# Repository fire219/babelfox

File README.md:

**NOTE: This project is not quite ready for prime time. Everything could be subject to change; build at your own risk. More documentation will come on full release.**

## What is this?
**BabelFox** is a project to create an energy efficient yet high performance Meshtastic "remote gateway node" -- one which not only has a wide TX/RX range on the mesh, but also can bridge the gap to other communication protocols, *without the need for any additional equipment*. It is equipped with a LoRA module based on the **Semtech LR1121** chip, which not only provides better RX performance than the standard SX1262 used by most Meshtastic hardware, but also includes 2.4GHz LoRA capability. It is also equipped with a **SIMCom SIM7022** LTE modem, which provides low power NB-IoT internet connectivity, with global cellular band support.

## Specifications
**Form factor:** RPi compatible (85x56mm, with 58x49mm spaced mounting holes)

**Main Processor:** Luckfox Pico (based on Rockchip RV1103)

**LoRA Radio:** EByte E80-900 (based on Semtech LR1121)

**900MHz Amplifier:** EByte E21-900 1W PA/LNA

**Cell Radio:** SIMCom SIM7022

**Max LoRA TX Power:** 30dBm @ 900MHz, 13dBm @ 2.4GHz

**Power Source:** USB-C (5V only), 3.7V LiPo, 8-18V VDC

**Power Consumption:** ~5W peak, <3W nominal

## License

**BabelFox** is licensed under the CERN OHL v2 Strongly Reciprocal license. See the *LICENSE* file for more information.

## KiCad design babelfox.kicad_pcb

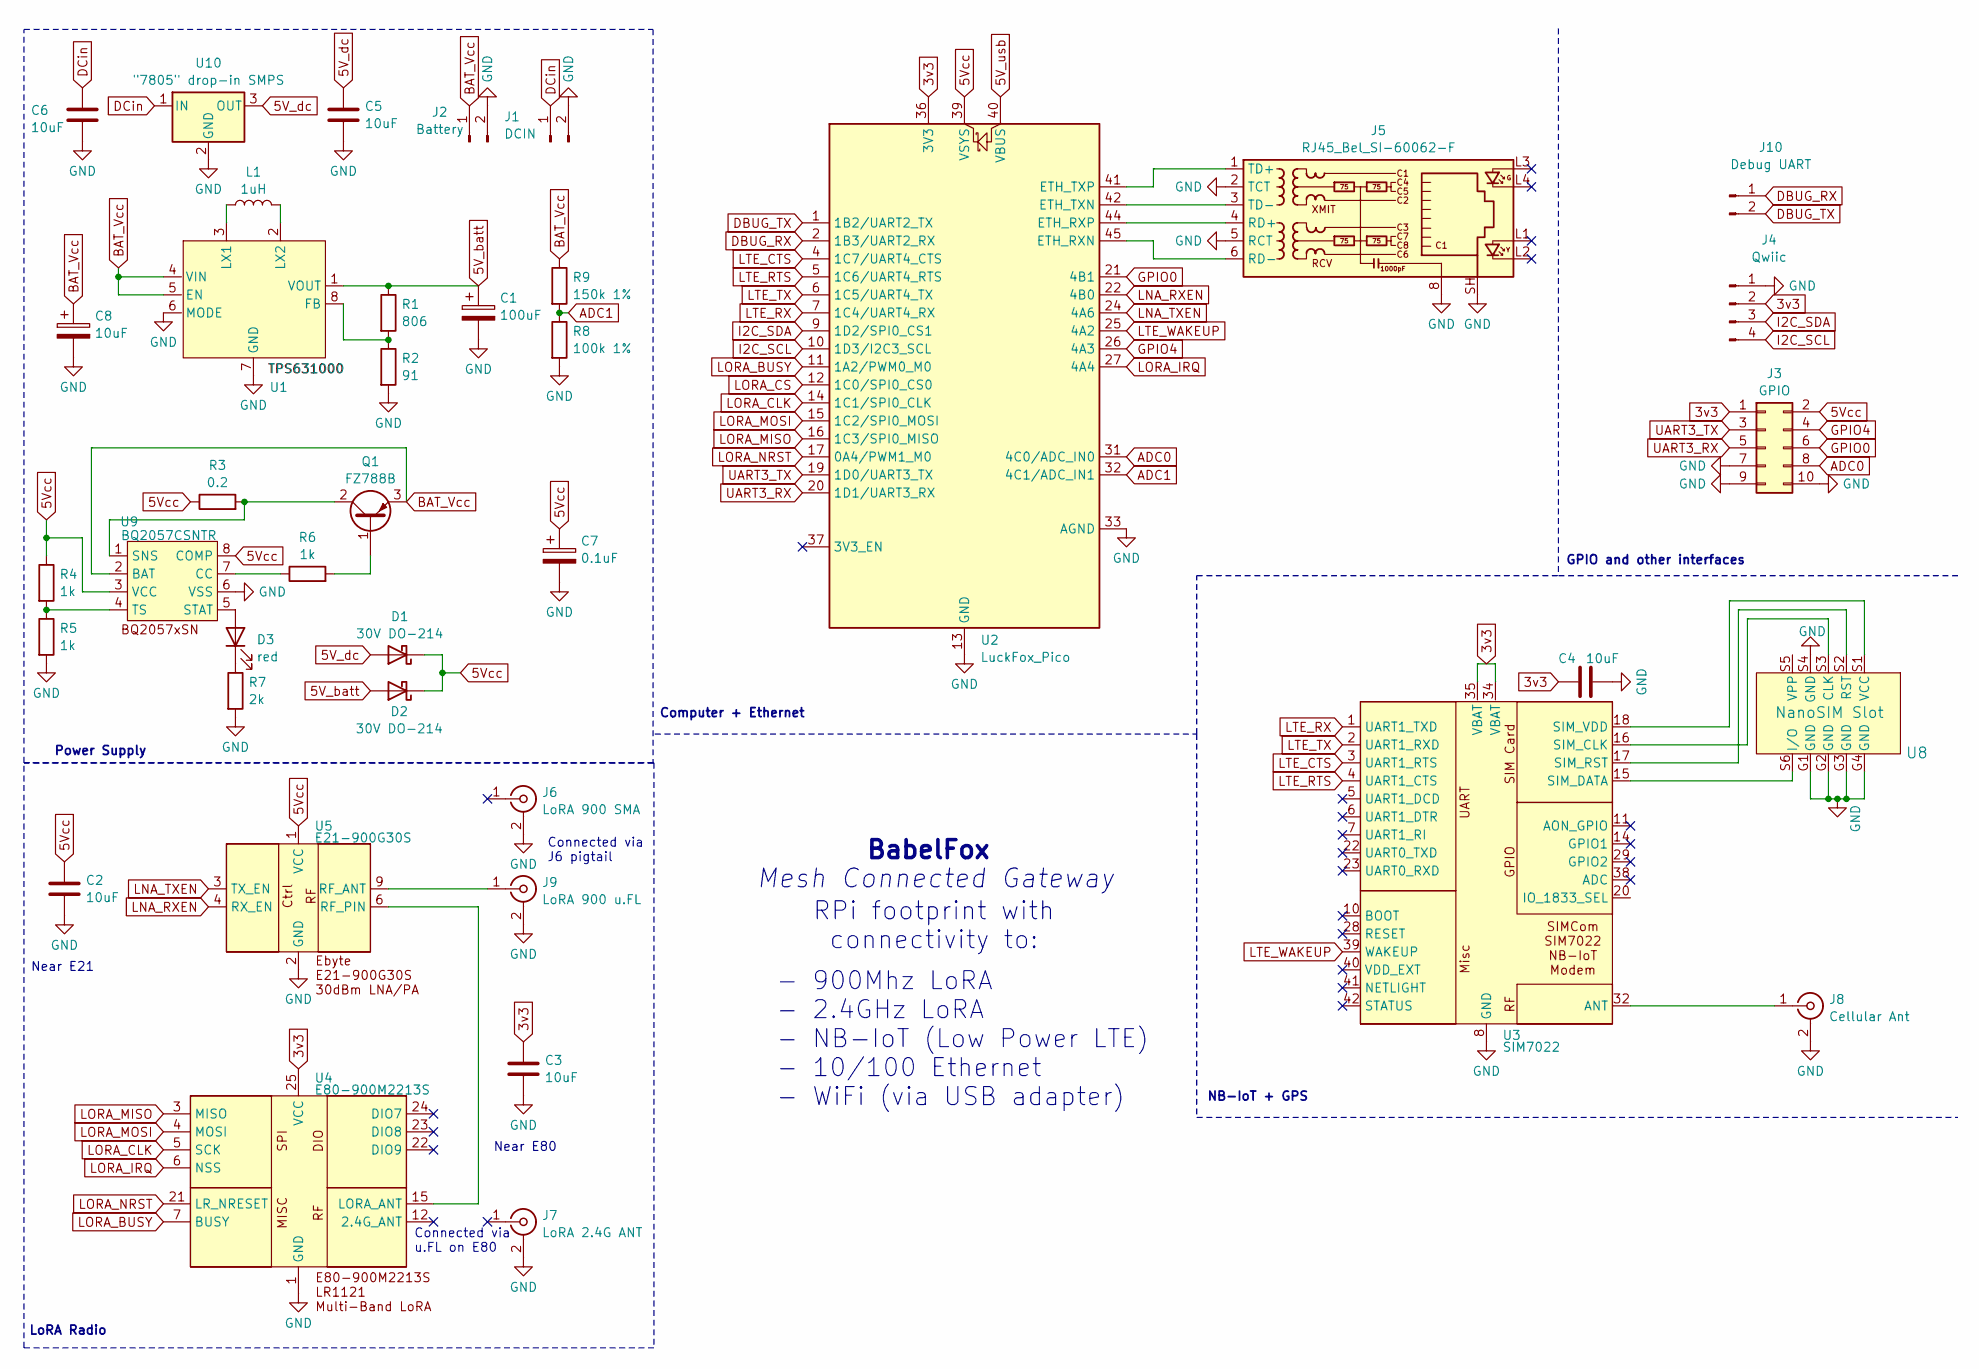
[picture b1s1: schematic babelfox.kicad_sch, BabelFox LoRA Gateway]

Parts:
C1: 100uF; C_0805_2012Metric_Pad1.18x1.45mm_HandSolder; LCSC C141660
C2, C3, C4, C5, C6, C8: 10uF; C_0805_2012Metric_Pad1.18x1.45mm_HandSolder; LCSC C15850
C7: 0.1uF; C_0805_2012Metric_Pad1.18x1.45mm_HandSolder; LCSC C17604
D1, D2: 30V DO-214; D_SMA_Handsoldering; LCSC C511853
D3: red; LED_0805_2012Metric_Pad1.15x1.40mm_HandSolder; LCSC C5156920
J1: DCIN; JST_EH_B2B-EH-A_1x02_P2.50mm_Vertical
J2: Battery; Molex_PicoBlade_53047-0210_1x02_P1.25mm_Vertical
J3: GPIO; PinHeader_2x05_P2.54mm_Vertical
J4: Qwiic; JST_SH_BM04B-SRSS-TB_1x04-1MP_P1.00mm_Vertical
J5: RJ45_Bel_SI-60062-F
J6: LoRA 900 SMA; SMA-TH_2LC15SF025
J7: LoRA 2.4G ANT; SMA-TH_2LC15SF025
J8: Cellular Ant; SMA_Amphenol_132203-12_Horizontal
J9: LoRA 900 u.FL; U.FL_Hirose_U.FL-R-SMT-1_Vertical; LCSC C88373
J10: Debug UART; PinSocket_1x02_P2.54mm_Vertical
L1: 1uH; L_1008_2520Metric_Pad1.43x2.20mm_HandSolder; LCSC C76827
Q1: FZ788B; SOT-223; LCSC C141330
R1: 806; R_0805_2012Metric_Pad1.20x1.40mm_HandSolder; LCSC C2999620
R2: 91; R_0805_2012Metric_Pad1.20x1.40mm_HandSolder; LCSC C4407
R3: 0.2; R_0805_2012Metric_Pad1.20x1.40mm_HandSolder; LCSC C44051
R4, R5, R6: 1k; R_0805_2012Metric_Pad1.20x1.40mm_HandSolder; LCSC C17513
R7: 2k; R_0805_2012Metric_Pad1.20x1.40mm_HandSolder
R8: 100k 1%; R_0805_2012Metric_Pad1.20x1.40mm_HandSolder; LCSC C25611
R9: 150k 1%; R_0805_2012Metric_Pad1.20x1.40mm_HandSolder; LCSC C17470
U1: TPS631000; SOT-583-8; LCSC C5219190
U2: LuckFox_Pico
U3: SIM7022; SIMCom_SIM7022
U4: E80-900M2213S; E80-x00M2213S
U5: E21-900G30S; E21-x00G30S
U8: NanoSIM Slot; 1042240820_MOL; LCSC C585349
U9: BQ2057CSNTR; SOIC-8_3.9x4.9mm_P1.27mm; LCSC C2866550
U10: "7805" drop-in SMPS; Converter_DCDC_RECOM_R-78E-0.5_THT

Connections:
3v3: C3.1, C4.1, J3.1, J4.2, U2.36 (3V3), U3.34 (VBAT), U3.35 (VBAT), U4.25 (VCC)
5V_batt: C1.1, D2.2 (A), R1.1, U1.1 (VOUT)
5V_dc: C5.1, D1.2 (A), U10.3 (OUT)
5V_usb: U2.40 (VBUS)
5Vcc: C2.1, C7.1, D1.1 (K), D2.1 (K), J3.2, R3.1, R4.1, U2.39 (VSYS), U5.1 (VCC), U9.3 (VCC), U9.8 (COMP)
ADC0: J3.8, U2.31 (4C0/ADC_IN0)
ADC1: R8.1, R9.2, U2.32 (4C1/ADC_IN1)
BAT_Vcc: C8.1, J2.1, Q1.3 (E), R9.1, U1.4 (VIN), U1.5 (EN), U9.2 (BAT)
DBUG_RX: J10.1, U2.2 (1B3/UART2_RX)
DBUG_TX: J10.2, U2.1 (1B2/UART2_TX)
DCin: C6.1, J1.1, U10.1 (IN)
GND: C1.2, C2.2, C3.2, C4.2, C5.2, C6.2, C7.2, C8.2, J1.2, J2.2, J3.7, J3.9, J3.10, J4.1, J5.2 (TCT), J5.5 (RCT), J5.8, J5.SH, J6.2 (Ext), J7.2 (Ext), J8.2 (Ext), J9.2 (Ext), R2.2, R5.2, R7.2, R8.2, U1.6 (MODE), U1.7 (GND), U2.3 (GND), U2.8 (GND), U2.13 (GND), U2.18 (GND), U2.23 (GND), U2.28 (GND), U2.33 (AGND), U2.38 (GND), U2.43 (GND), U3.8 (GND), U3.13 (GND), U3.19 (GND), U3.21 (GND), U3.27 (GND), U3.30 (GND), U3.31 (GND), U3.33 (GND), U3.36 (GND), U3.37 (GND), U4.1 (GND), U4.8 (GND), U4.11 (GND), U4.13 (GND), U4.14 (GND), U4.16 (GND), U4.19 (GND), U4.26 (GND), U5.2 (GND), U5.5 (GND), U5.7 (GND), U5.8 (GND), U5.10 (GND), U8.G1 (GND), U8.G2 (GND), U8.G3 (GND), U8.G4 (GND), U8.S4 (GND), U9.6 (VSS), U10.2 (GND)
GPIO0: J3.6, U2.21 (4B1)
GPIO4: J3.4, U2.26 (4A3)
I2C_SCL: J4.4, U2.10 (1D3/I2C3_SCL)
I2C_SDA: J4.3, U2.9 (1D2/SPI0_CS1)
LNA_RXEN: U2.22 (4B0), U5.4 (RX_EN)
LNA_TXEN: U2.24 (4A6), U5.3 (TX_EN)
LORA_BUSY: U2.11 (1A2/PWM0_M0), U4.7 (BUSY)
LORA_CLK: U2.14 (1C1/SPI0_CLK), U4.5 (SCK)
LORA_CS: U2.12 (1C0/SPI0_CS0)
LORA_IRQ: U2.27 (4A4), U4.6 (NSS)
LORA_MISO: U2.16 (1C3/SPI0_MISO), U4.3 (MISO)
LORA_MOSI: U2.15 (1C2/SPI0_MOSI), U4.4 (MOSI)
LORA_NRST: U2.17 (0A4/PWM1_M0), U4.21 (LR_NRESET)
LTE_CTS: U2.4 (1C7/UART4_CTS), U3.3 (UART1_RTS)
LTE_RTS: U2.5 (1C6/UART4_RTS), U3.4 (UART1_CTS)
LTE_RX: U2.7 (1C4/UART4_RX), U3.1 (UART1_TXD)
LTE_TX: U2.6 (1C5/UART4_TX), U3.2 (UART1_RXD)
LTE_WAKEUP: U2.25 (4A2), U3.39 (WAKEUP)
unnamed: D3.2 (A), U9.5 (STAT)
unnamed: D3.1 (K), R7.1
unnamed: J5.4 (RD+), U2.44 (ETH_RXP)
unnamed: J5.6 (RD-), U2.45 (ETH_RXN)
unnamed: J5.1 (TD+), U2.41 (ETH_TXP)
unnamed: J5.3 (TD-), U2.42 (ETH_TXN)
unnamed: J8.1 (In), U3.32 (ANT)
unnamed: J9.1 (In), U5.9 (RF_ANT)
unnamed: Q1.1 (B), R6.2
unnamed: Q1.2 (C), R3.2, U9.1 (SNS)
unnamed: R1.2, R2.1, U1.8 (FB)
unnamed: L1.1, U1.3 (LX1)
unnamed: L1.2, U1.2 (LX2)
unnamed: U3.16 (SIM_CLK), U8.S3 (CLK)
unnamed: U3.15 (SIM_DATA), U8.S6 (I/O)
unnamed: U3.17 (SIM_RST), U8.S2 (RST)
unnamed: U3.18 (SIM_VDD), U8.S1 (VCC)
unnamed: U4.15 (LORA_ANT), U5.6 (RF_PIN)
unnamed: R6.1, U9.7 (CC)
unnamed: R4.2, R5.1, U9.4 (TS)
UART3_RX: J3.5, U2.20 (1D1/UART3_RX)
UART3_TX: J3.3, U2.19 (1D0/UART3_TX)

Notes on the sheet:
Connected via J6 pigtail
Near E21
RPi footprint with connectivity to:
NB-IoT + GPS
Mesh Connected Gateway
Computer + Ethernet
Power Supply
Near E80
LoRA Radio
Connected via u.FL on E80
BabelFox
- 900Mhz LoRA - 2.4GHz LoRA - NB-IoT (Low Power LTE) - 10/100 Ethernet - WiFi (via USB adapter)
GPIO and other interfaces

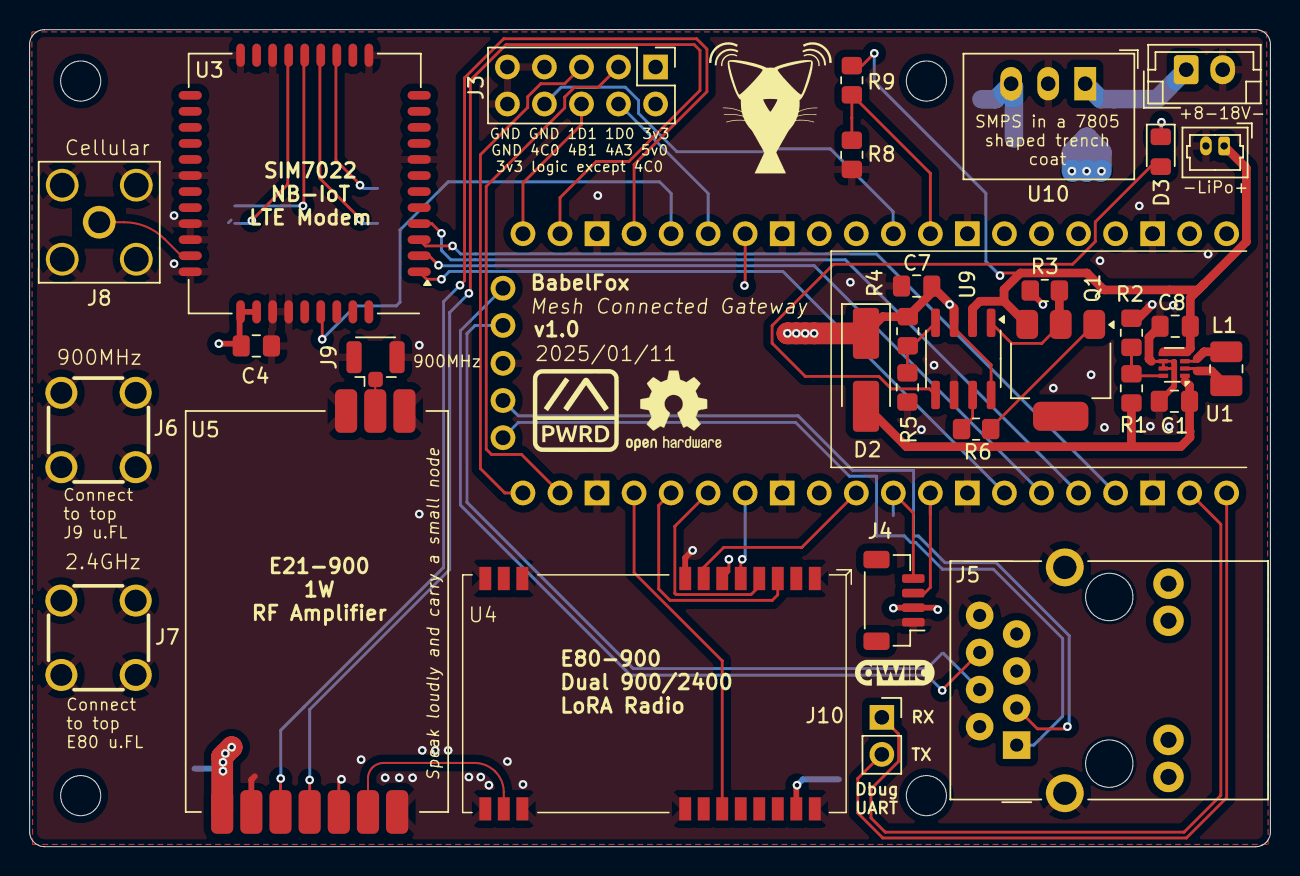
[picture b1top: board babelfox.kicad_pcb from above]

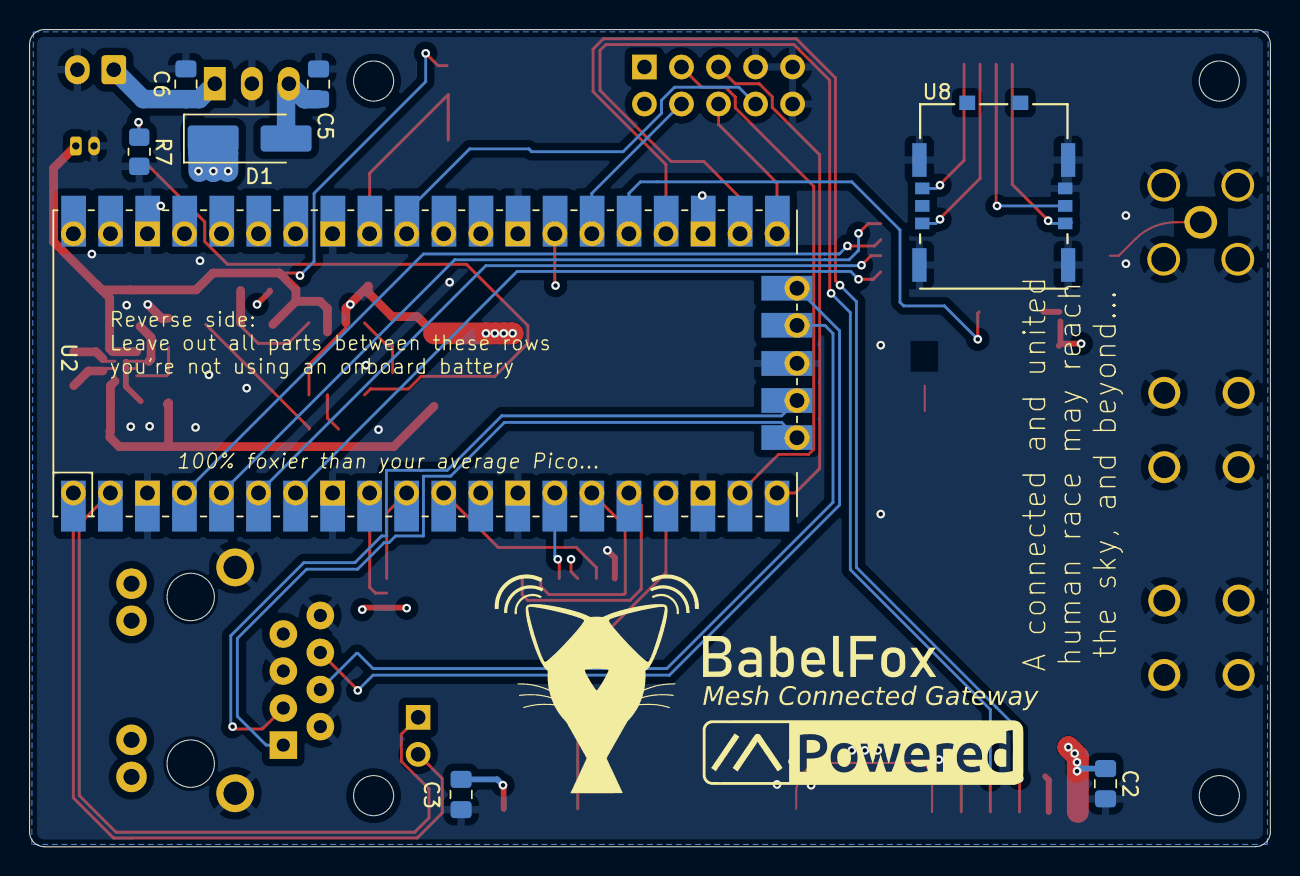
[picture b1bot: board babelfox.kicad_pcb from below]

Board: 4 copper layers, 85.1 x 56.0 mm, 43 parts (10 on the bottom side), 50 nets.

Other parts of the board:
.: LOGO; babelfox_logo_9x9
.#2: LOGO; m_powered2
.#3: LOGO; babelfox_logo

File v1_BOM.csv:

"Reference","Value","Footprint","Qty","Notes"
"C1","100uF","Capacitor_SMD:C_0805_2012Metric_Pad1.18x1.45mm_HandSolder","1","6V, DNP if no battery circuit"
"C2,C3,C4,C5,C6,C8","10uF","Capacitor_SMD:C_0805_2012Metric_Pad1.18x1.45mm_HandSolder","6","25V, qty 5 if no battery circuit"
"C7","0.1uF","Capacitor_SMD:C_0805_2012Metric_Pad1.18x1.45mm_HandSolder","1","DNP if no battery circuit"
"D1,D2","30V DO-214","Diode_SMD:D_SMA_Handsoldering","2","30V"
"D3","red","LED_SMD:LED_0805_2012Metric_Pad1.15x1.40mm_HandSolder","1",""
"J1","DCIN","Connector_JST:JST_EH_B2B-EH-A_1x02_P2.50mm_Vertical","1",""
"J2","Battery","Connector_Molex:Molex_PicoBlade_53047-0210_1x02_P1.25mm_Vertical","1","DNP if no battery circuit"
"J3","GPIO","Connector_PinHeader_2.54mm:PinHeader_2x05_P2.54mm_Vertical","1",""
"J4","Qwiic","Connector_JST:JST_SH_BM04B-SRSS-TB_1x04-1MP_P1.00mm_Vertical","1",""
"J5","RJ45_Bel_SI-60062-F","Connector_RJ:RJ45_Bel_SI-60062-F","1",""
"J6","LoRA 900 SMA","SMA-uFL jack:SMA-TH_2LC15SF025","1","SMA with pre-wired u.FL/IPEX pigtail"
"J7","LoRA 2.4G ANT","SMA-uFL jack:SMA-TH_2LC15SF025","1","SMA with pre-wired u.FL/IPEX pigtail"
"J8","Cellular Ant","Connector_Coaxial:SMA_Amphenol_132203-12_Horizontal","1",""
"J9","LoRA 900 u.FL","Connector_Coaxial:U.FL_Hirose_U.FL-R-SMT-1_Vertical","1",""
"J10","Debug UART","Connector_PinSocket_2.54mm:PinSocket_1x02_P2.54mm_Vertical","1",""
"L1","1uH","Inductor_SMD:L_1008_2520Metric_Pad1.43x2.20mm_HandSolder","1","Isat > 3A, DNP if no battery circuit"
"Q1","FZ788B","Package_TO_SOT_SMD:SOT-223","1","DNP if no battery circuit"
"R1","806","Resistor_SMD:R_0805_2012Metric_Pad1.20x1.40mm_HandSolder","1","DNP if no battery circuit"
"R2","91","Resistor_SMD:R_0805_2012Metric_Pad1.20x1.40mm_HandSolder","1","DNP if no battery circuit"
"R3","0.2","Resistor_SMD:R_0805_2012Metric_Pad1.20x1.40mm_HandSolder","1","DNP if no battery circuit"
"R4,R5,R6","1k","Resistor_SMD:R_0805_2012Metric_Pad1.20x1.40mm_HandSolder","3","DNP if no battery circuit"
"R7","2k","Resistor_SMD:R_0805_2012Metric_Pad1.20x1.40mm_HandSolder","1","DNP if no battery circuit"
"R8","100k 1%","Resistor_SMD:R_0805_2012Metric_Pad1.20x1.40mm_HandSolder","1","DNP if no battery circuit"
"R9","150k 1%","Resistor_SMD:R_0805_2012Metric_Pad1.20x1.40mm_HandSolder","1","DNP if no battery circuit"
"U1","TPS631000","Package_TO_SOT_SMD:SOT-583-8","1","DNP if no battery circuit"
"U2","LuckFox_Pico","LuckFox_Pico:LuckFox_Pico","1",""
"U3","SIM7022","SIM7022:SIMCom_SIM7022","1",""
"U4","E80-900M2213S","E80-x00M2213S:E80-x00M2213S","1",""
"U5","E21-900G30S","E21-x00G30S:E21-x00G30S","1",""
"U8","NanoSIM Slot","simcard:1042240820_MOL","1",""
"U9","BQ2057CSNTR","Package_SO:SOIC-8_3.9x4.9mm_P1.27mm","1","DNP if no battery circuit"
"U10","""7805"" drop-in SMPS","Converter_DCDC:Converter_DCDC_RECOM_R-78E-0.5_THT","1",">1.5A output recommended"

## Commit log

2025-01-01 prerelease, may contain dragons
2025-01-01 markdown kinda sucks
2025-01-02 board cleanup, add images
2025-01-02 neutral color logo for light/dark mode github compat
2025-01-02 typo
2025-01-06 Jan 5 progress, update license to OHL-S
2025-01-07 LCSC IDs; OSHW silkscreen; new imgs
2025-01-08 LCSC inductor... but i'm not doing LCSC anymore
2025-01-11 board as sent to JLC 1/11
2025-03-02 push BOM
